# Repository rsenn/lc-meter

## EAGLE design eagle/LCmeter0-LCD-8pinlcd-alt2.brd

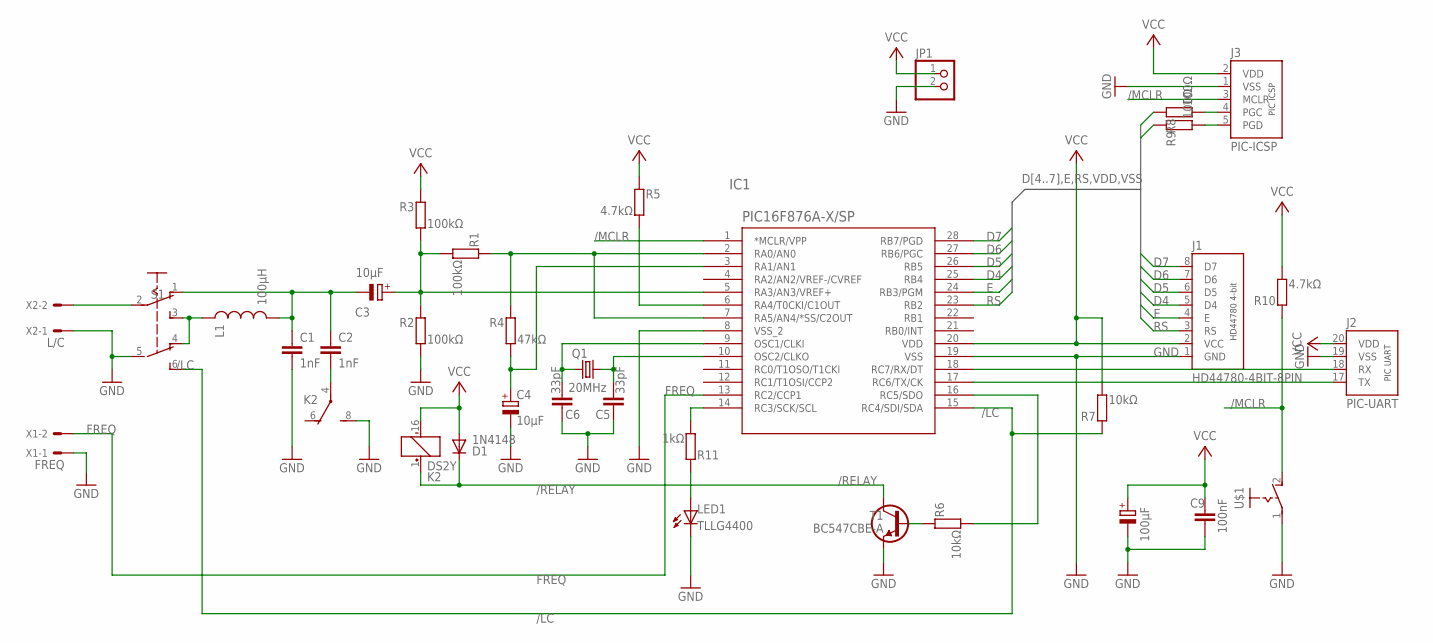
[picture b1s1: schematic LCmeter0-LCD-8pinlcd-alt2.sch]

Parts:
C1, C2: 1nF; C050-020X036
C3, C4: 10μF; E2,5-4
C5, C6: 33pF; C025-020X036
C7: 100μF; E2,5-6
C9: 100nF; C025-024X044
D1: 1N4148; DO34-7
IC1: PIC16F876A-X/SP; DIL28-3
J1: HD44780-4BIT-8PIN; CONN-8P
J2: PIC-UART
J3: PIC-ICSP; CONN-5P
JP1: PINHD-1X2; 1X02
K2: DS2Y
L1: 100μH; L-8R
LED1: TLLG4400; LED3MM
Q1: 20MHz; HC49
R1, R2, R3: 100kΩ; 0202/7
R4: 47kΩ; 0202/7
R5, R10: 4.7kΩ; 0202/7
R6: 10kΩ; 0202/7
R7: 10kΩ; 0202/10
R8, R9: 100Ω; 0202/5
R11: 1kΩ; 0202/5
S1: SL-SW-2P-2T; SLSW-2P2T
T1: BC547CBE-A; TO92-CBE-A
U$1: PB-1P-1T; PB-1P1T
X1: FREQ; 70543-02
X2: L/C; 70543-02

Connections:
/LC: IC1.15 (RC4/SDI/SDA), R7.2, S1.6 (S1)
/MCLR: IC1.1 (*MCLR/VPP), J3.3 (MCLR), R10.2, U$1.2 (S)
/RELAY: D1.C, K2.1 (+), T1.C
A0: IC1.2 (RA0/AN0), IC1.7 (RA5/AN4/*SS/C2OUT), R1.2, R4.2
A1: C4.+, IC1.3 (RA1/AN1), R4.1
A3: C3.+, IC1.5 (RA3/AN3/VREF+), R1.1, R2.2, R3.1
A4: IC1.6 (RA4/T0CKI/C1OUT), R5.1
C2_CON: C2.2, K2.4
D4: IC1.25 (RB4), J1.5 (D4)
D5: IC1.26 (RB5), J1.6 (D5)
D6: IC1.27 (RB6/PGC), J1.7 (D6), R9.2
D7: IC1.28 (RB7/PGD), J1.8 (D7), R8.2
E: IC1.24 (RB3/PGM), J1.4 (E)
FREQ: IC1.13 (RC2/CCP1), X1.2
GND: C1.2, C4.-, C5.1, C6.1, C7.-, C9.2, IC1.8 (VSS_2), IC1.19 (VSS), J1.1 (GND), J2.19 (VSS), J3.1 (VSS), JP1.2, K2.8 (S), LED1.K (C), R2.1, S1.5 (P1), T1.E, U$1.1, X1.1, X2.1
M+: S1.2, X2.2
unnamed: J3.4 (PGC), R8.1
unnamed: C1.1, C2.1, C3.-, L1.P$2 (2), S1.1 (O)
unnamed: J3.5 (PGD), R9.1
unnamed: IC1.14 (RC3/SCK/SCL), R11.1
unnamed: R6.2, T1.B
unnamed: LED1.A, R11.2
unnamed: L1.P$1 (1), S1.3 (S), S1.4 (O1)
unnamed: IC1.17 (RC6/TX/CK), J2.17 (TX)
OSC1: C6.2, IC1.9 (OSC1/CLKI), Q1.1
OSC2: C5.2, IC1.10 (OSC2/CLKO), Q1.2
RC5: IC1.16 (RC5/SDO), R6.1
RS: IC1.23 (RB2), J1.3 (RS)
RX: IC1.18 (RC7/RX/DT), J2.18 (RX)
VCC: C7.+, C9.1, D1.A, IC1.20 (VDD), J1.2 (VCC), J2.20 (VDD), J3.2 (VDD), JP1.1, K2.16 (-), R3.2, R5.2, R7.1, R10.1

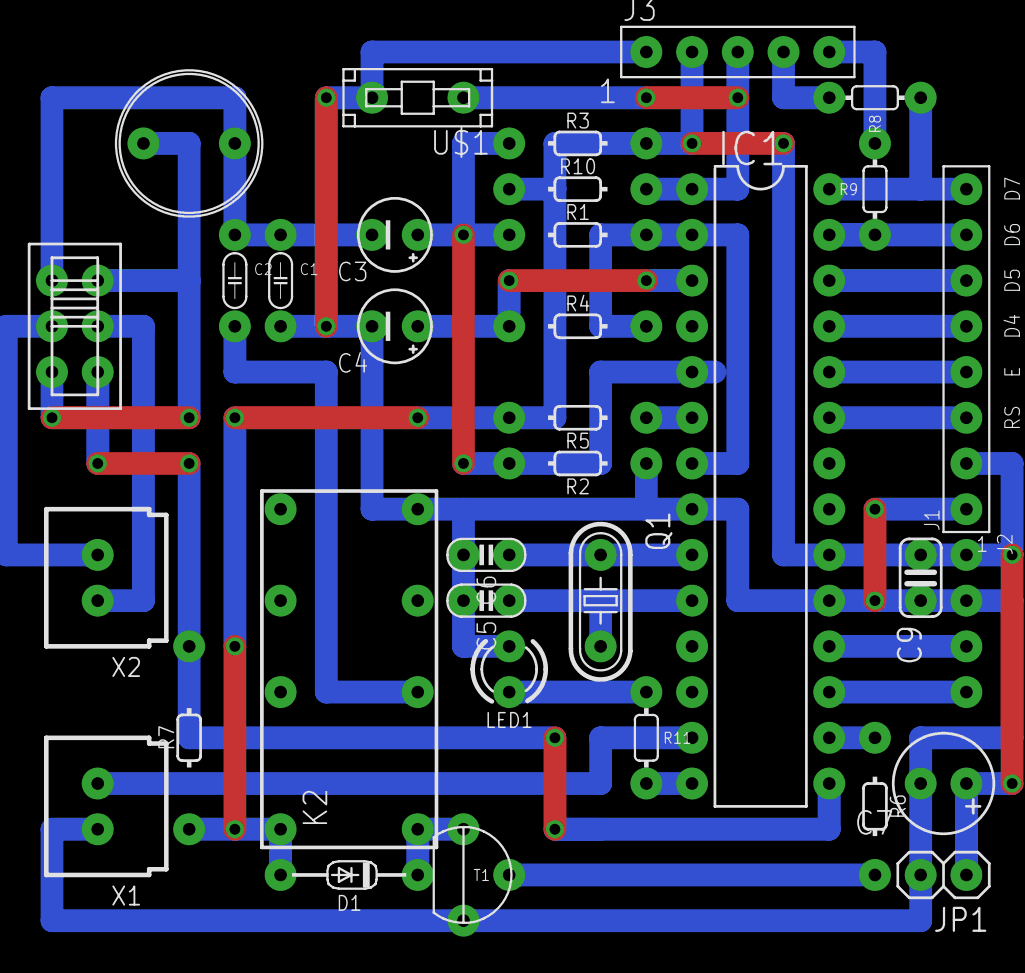
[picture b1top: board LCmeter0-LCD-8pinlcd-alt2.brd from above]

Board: 2 copper layers, 34 parts (0 on the bottom side), 30 nets.

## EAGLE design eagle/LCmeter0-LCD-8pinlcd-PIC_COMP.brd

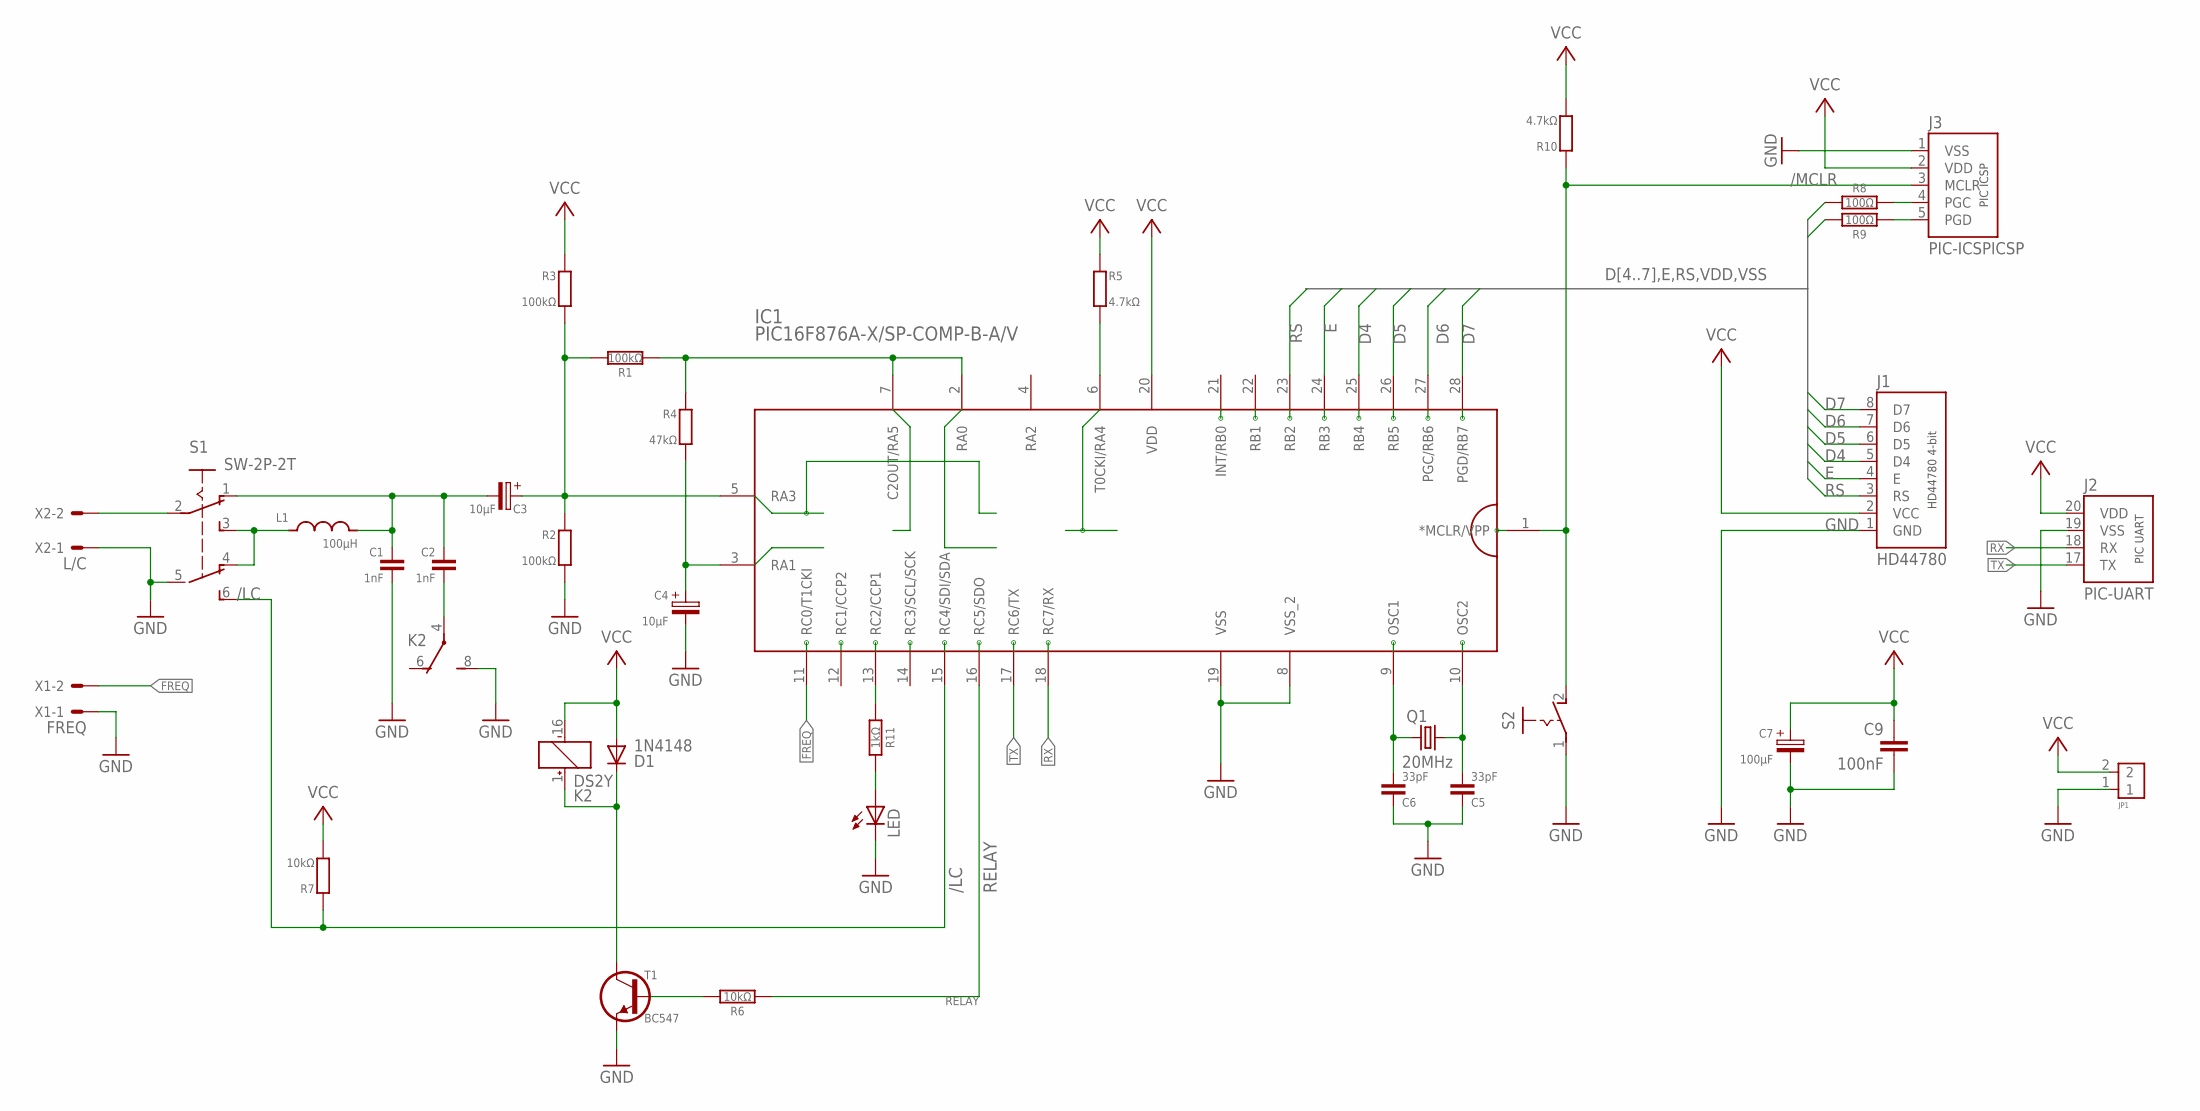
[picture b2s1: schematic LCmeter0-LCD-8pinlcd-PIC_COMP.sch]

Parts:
C1, C2: 1nF; C050-020X036
C3, C4: 10μF; E2,5-4
C5, C6: 33pF; C025-020X036
C7: 100μF; E2,5-5
C9: 100nF; C025-024X044
D1: 1N4148; DO34-7
IC1: PIC16F876A-X/SP-COMP-B-A/V; DIL28-3/V
J1: HD44780; CONN-8P
J2: PIC-UART
J3: PIC-ICSPICSP; PIC-ICSP
JP1: CONN-2P2P/V; CONN-2P-V
K2: DS2Y
L1: 100µH; L-02/5V
LED: TLLG4400; LED3MM
Q1: 20MHz; HC49
R1, R2, R3: 100kΩ; 0202/7
R4: 47kΩ; 0202/7
R5, R10: 4.7kΩ; 0202/7
R6: 10kΩ; 0202/7
R7: 10kΩ; 0202/10
R8, R9: 100Ω; 0202/5
R11: 1kΩ; 0202/5
S1: SW-2P-2T; SLSW-2P2T
S2: PB-1P-1T; PB-1P1T
T1: BC547; TO92-CBE-A
X1: FREQ; 70543-02
X2: L/C; 70543-02

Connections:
/LC: IC1.15 (RC4/SDI/SDA), R7.1, S1.6 (S1)
/MCLR: IC1.1 (*MCLR/VPP), J3.3 (MCLR), R10.1, S2.2 (S)
/RELAY: D1.C, K2.1 (+), T1.C
A0: IC1.2 (RA0), IC1.7 (C2OUT/RA5), R1.1, R4.1
A1: C4.+, IC1.3 (RA1), R4.2
A3: C3.+, IC1.5 (RA3), R1.2, R2.1, R3.2
A4: IC1.6 (T0CKI/RA4), R5.2
C2_CON: C2.2, K2.4
D4: IC1.25 (RB4), J1.5 (D4)
D5: IC1.26 (RB5), J1.6 (D5)
D6: IC1.27 (PGC/RB6), J1.7 (D6), R9.1
D7: IC1.28 (PGD/RB7), J1.8 (D7), R8.1
E: IC1.24 (RB3), J1.4 (E)
FREQ: IC1.11 (RC0/T1CKI), X1.2
GND: C1.2, C4.-, C5.1, C6.1, C7.-, C9.2, IC1.8 (VSS_2), IC1.19 (VSS), J1.1 (GND), J2.19 (VSS), J3.1 (VSS), JP1.1, K2.8 (S), LED.K (C), R2.2, S1.5 (P1), S2.1, T1.E, X1.1, X2.1
M+: S1.2, X2.2
unnamed: J3.4 (PGC), R8.2
unnamed: C1.1, C2.1, C3.-, L1.2, S1.1 (O)
unnamed: J3.5 (PGD), R9.2
unnamed: IC1.13 (RC2/CCP1), R11.2
unnamed: R6.1, T1.B
unnamed: LED.A, R11.1
unnamed: L1.1, S1.3 (S), S1.4 (O1)
OSC1: C6.2, IC1.9 (OSC1), Q1.1
OSC2: C5.2, IC1.10 (OSC2), Q1.2
RELAY: IC1.16 (RC5/SDO), R6.2
RS: IC1.23 (RB2), J1.3 (RS)
RX: IC1.18 (RC7/RX), J2.18 (RX)
TX: IC1.17 (RC6/TX), J2.17 (TX)
VCC: C7.+, C9.1, D1.A, IC1.20 (VDD), J1.2 (VCC), J2.20 (VDD), J3.2 (VDD), JP1.2, K2.16 (-), R3.1, R5.1, R7.2, R10.2

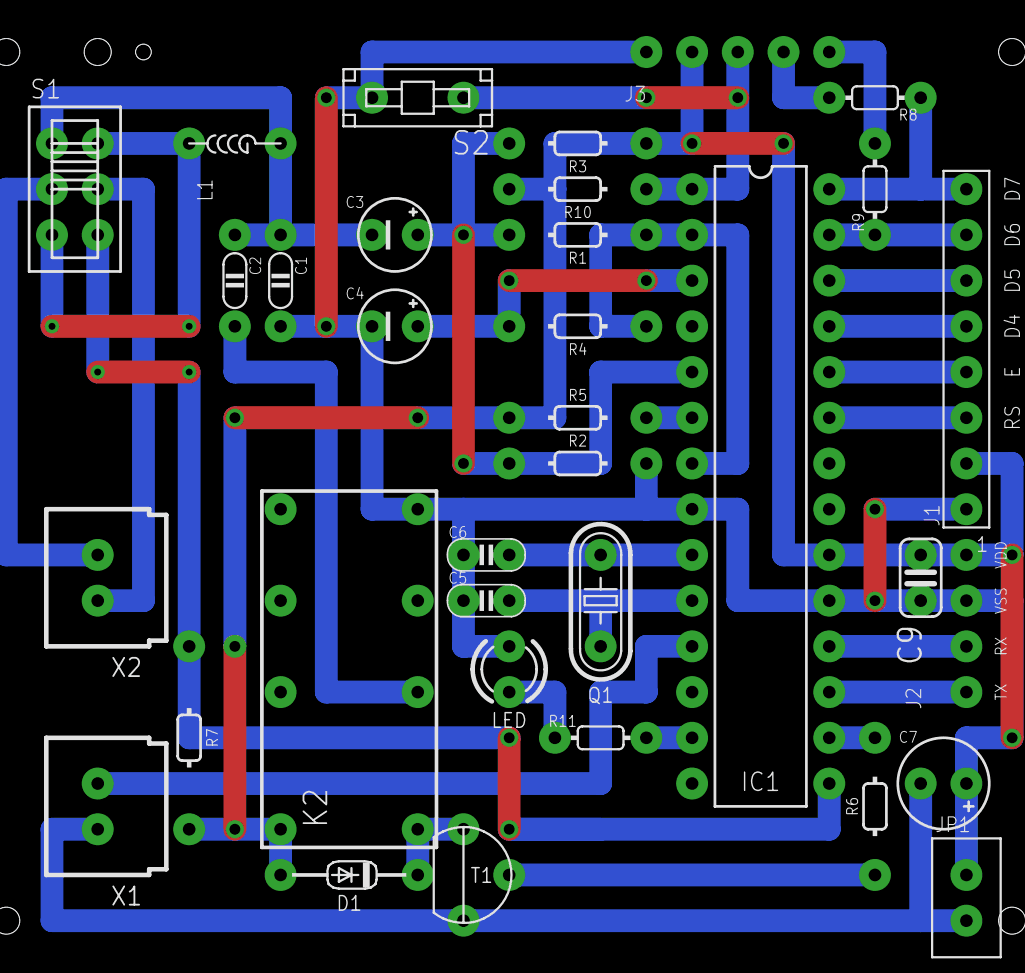
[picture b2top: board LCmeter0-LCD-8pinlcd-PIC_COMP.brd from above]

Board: 2 copper layers, 34 parts (0 on the bottom side), 30 nets.

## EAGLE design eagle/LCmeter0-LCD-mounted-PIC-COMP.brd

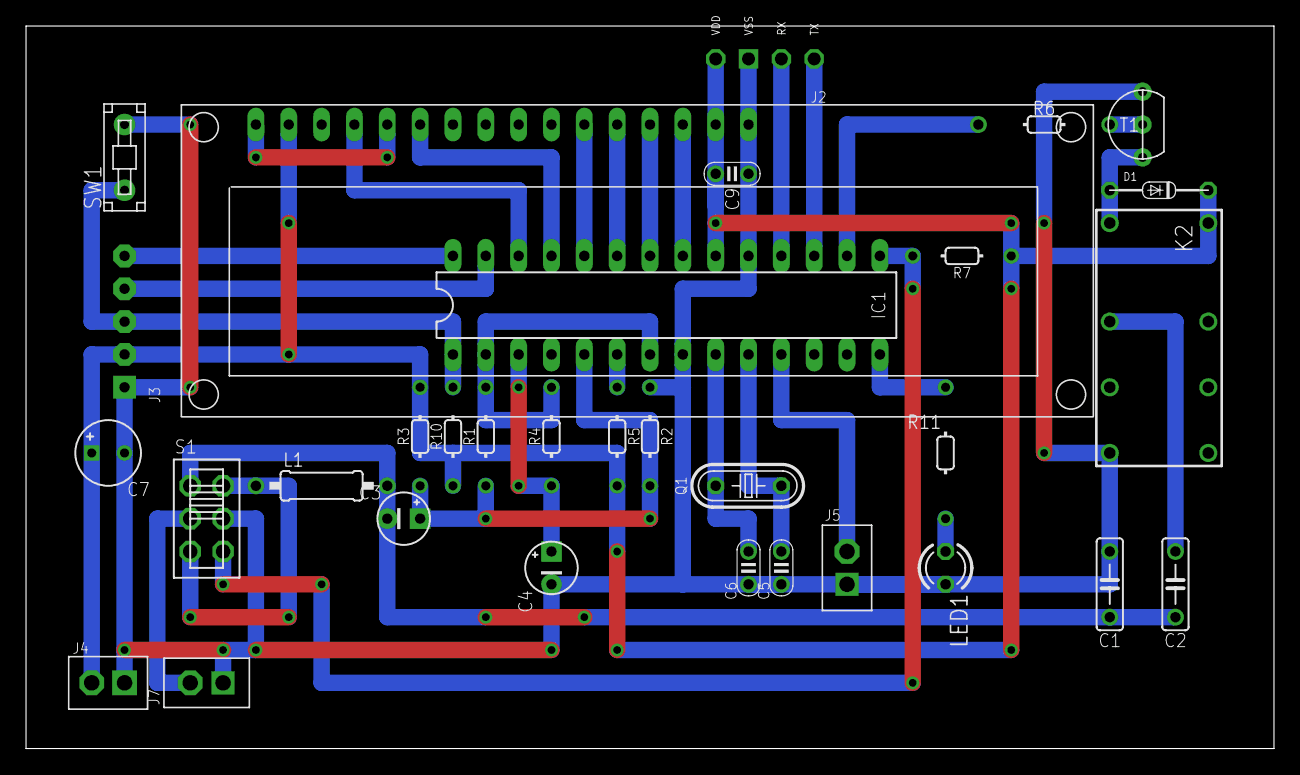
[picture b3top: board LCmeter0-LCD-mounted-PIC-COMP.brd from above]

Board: 2 copper layers, 96.5 x 55.9 mm, 32 parts (0 on the bottom side), 30 nets.

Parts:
C1, C2: 1nF; C050-025X060
C3, C4: 10μF; E2,5-4
C5, C6: 33pF; C025-020X036
C7: 100μF; E2,5-5
C9: 100nF; C025-020X036/V
D1: 1N4148; DO34-7
IC1: PIC16F876A; DIL28-3
J1: HD44780LM016L; LM016L-HD44780
J2: PIC-UART
J3: PIC-ICSP
J4: J4; CONN-2P
J5, J7: CONN-2P2P/V; CONN-2P-V
K2: DS2Y
L1: 82μH; 0207/10
LED1: TLLG4400; LED3MM
Q1: 20MHz; HC49
R1, R2, R3: 100kΩ; 0202/7
R4: 47kΩ; 0202/7
R5, R10: 4.7kΩ; 0202/7
R6: 10kΩ; 0202/10
R7: 10kΩ; 0202/7
R11: 1kΩ; 0202/10-V
S1: SL-SW-2P-2T; SLSW-2P2T
SW1: PB-1P-1T; PB-1P1T
T1: BC547; TO92-CBE

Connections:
/LC: IC1.15, R7.2, S1.6
/MCLR: IC1.1, J3.3, R10.2, SW1.2
/RELAY: D1.A, K2.1, T1.C
A0: IC1.2, IC1.7, R1.2, R4.2
A1: C4.+, IC1.3, R4.1
A3: C3.+, IC1.5, R1.1, R2.2, R3.1
A4: IC1.6, R5.1
C2_CON: C2.2, K2.4
FREQ: IC1.11, J5.2
GND: C1.2, C4.-, C5.1, C6.1, C7.-, C9.1, IC1.8, IC1.19, J1.1, J1.5, J2.19, J3.1, J4.1, J5.1, J7.1, K2.8, LED1.K, R2.1, S1.5, SW1.1, T1.E
IN+: J7.2, S1.2
unnamed: LED1.A, R11.1
unnamed: C1.1, C2.1, C3.-, L1.2, S1.1
unnamed: IC1.14, R11.2
unnamed: R6.2, T1.B
unnamed: L1.1, S1.3, S1.4
unnamed: IC1.16, R6.1
unnamed: IC1.18, J2.18
unnamed: IC1.17, J2.17
OSC1: C6.2, IC1.9, Q1.2
OSC2: C5.2, IC1.10, Q1.1
RB0: IC1.21, J1.14
RB1: IC1.22, J1.13
RB2: IC1.23, J1.12
RB3: IC1.24, J1.11
RB4: IC1.25, J1.6
RB5: IC1.26, J1.4
RB6: IC1.27, J3.4
RB7: IC1.28, J3.5
VCC: C7.+, C9.2, D1.C, IC1.20, J1.2, J2.20, J3.2, J4.2, K2.16, R3.2, R5.2, R7.1, R10.1

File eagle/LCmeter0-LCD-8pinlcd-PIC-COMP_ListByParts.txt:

Part Value                   Attributes Package       Description                                                    Part Num,,
C1   1nF                                C050-025X060  CAPACITOR, European symbol                                     *       ,
C2   1nF                                C050-025X060  CAPACITOR, European symbol                                     *       ,
C3   10µF                               E2,5-4        POLARIZED CAPACITOR, European symbol                           *       
C4   10µF                               E2,5-4        POLARIZED CAPACITOR, European symbol                           *       
C5   33pF                               C025-020X036  CAPACITOR, European symbol                                     *       ,
C6   33pF                               C025-020X036  CAPACITOR, European symbol                                     *       ,
C7   100µF                              E2,5-5        POLARIZED CAPACITOR, European symbol                           *       
C8   22pF                               C050-020X036  CAPACITOR, European symbol                                     *       ,
C9   100nF                              C025-024X044  CAPACITOR, European symbol                                     *       ,
D1   1N4148                             DO34-7                                                                       *       ,,
D2   1N4148                             DO34-12V                                                                     *       ,,
IC1  PIC16F876A                         DIL28-3                                                                      *       ,,
J1   HD44780-4BITLCD44780-8P            CONN-LCD44780                                                                *       ,,
J2   PIC-UART                           PIC-UART                                                                     *       ,,
J3   PIC-ICSP                           PIC-ICSP                                                                     *       ,,
J4   J4                                 CONN-2P                                                                      *       ,,
J5   CONN-2P2P/V                        CONN-2P-V                                                                    *       ,,
J7   CONN-2P2P/V                        CONN-2P-V                                                                    *       ,,
K2   DS2Y                               DS2Y          MINIATURE RELAY NAiS                                           *       ,,
L1   68µH                               L-09R                                                                        *       ,,
LED1 TLLG4400                           LED3MM        Low Current (2mA) LED 3 mm Tinted Diffused Package color GREEN *       ,,
Q1   20MHz                              HC49                                                                         *       ,,
R1   100kO                              0202/7        RESISTOR, European symbol                                      *       ,
R2   100kO                              0202/7        RESISTOR, European symbol                                      *       ,
R3   100kO                              0202/7        RESISTOR, European symbol                                      *       ,
R4   47kO                               0202/7        RESISTOR, European symbol                                      *       ,
R5   4.7kO                              0202/7        RESISTOR, European symbol                                      *       ,
R6   10k                                0202/7-V      RESISTOR, European symbol                                      *       ,
R7   10kO                               0202/10       RESISTOR, European symbol                                      *       ,
R8   100                                0202/7        RESISTOR, European symbol                                      *       ,
R9   100                                0202/5-V      RESISTOR, European symbol                                      *       ,
R10  4.7kO                              0202/7        RESISTOR, European symbol                                      *       ,
R11  1k                                 0202/5-V      RESISTOR, European symbol                                      *       ,
S1   SL-SW-2P-2T-H                      SLSW-2P2T-H                                                                  *       ,,
SW1  PB-1P-1T                           PB-1P1T                                                                      *       ,,
T1   BC547                              TO92-CBE-A                                                                   *       ,,

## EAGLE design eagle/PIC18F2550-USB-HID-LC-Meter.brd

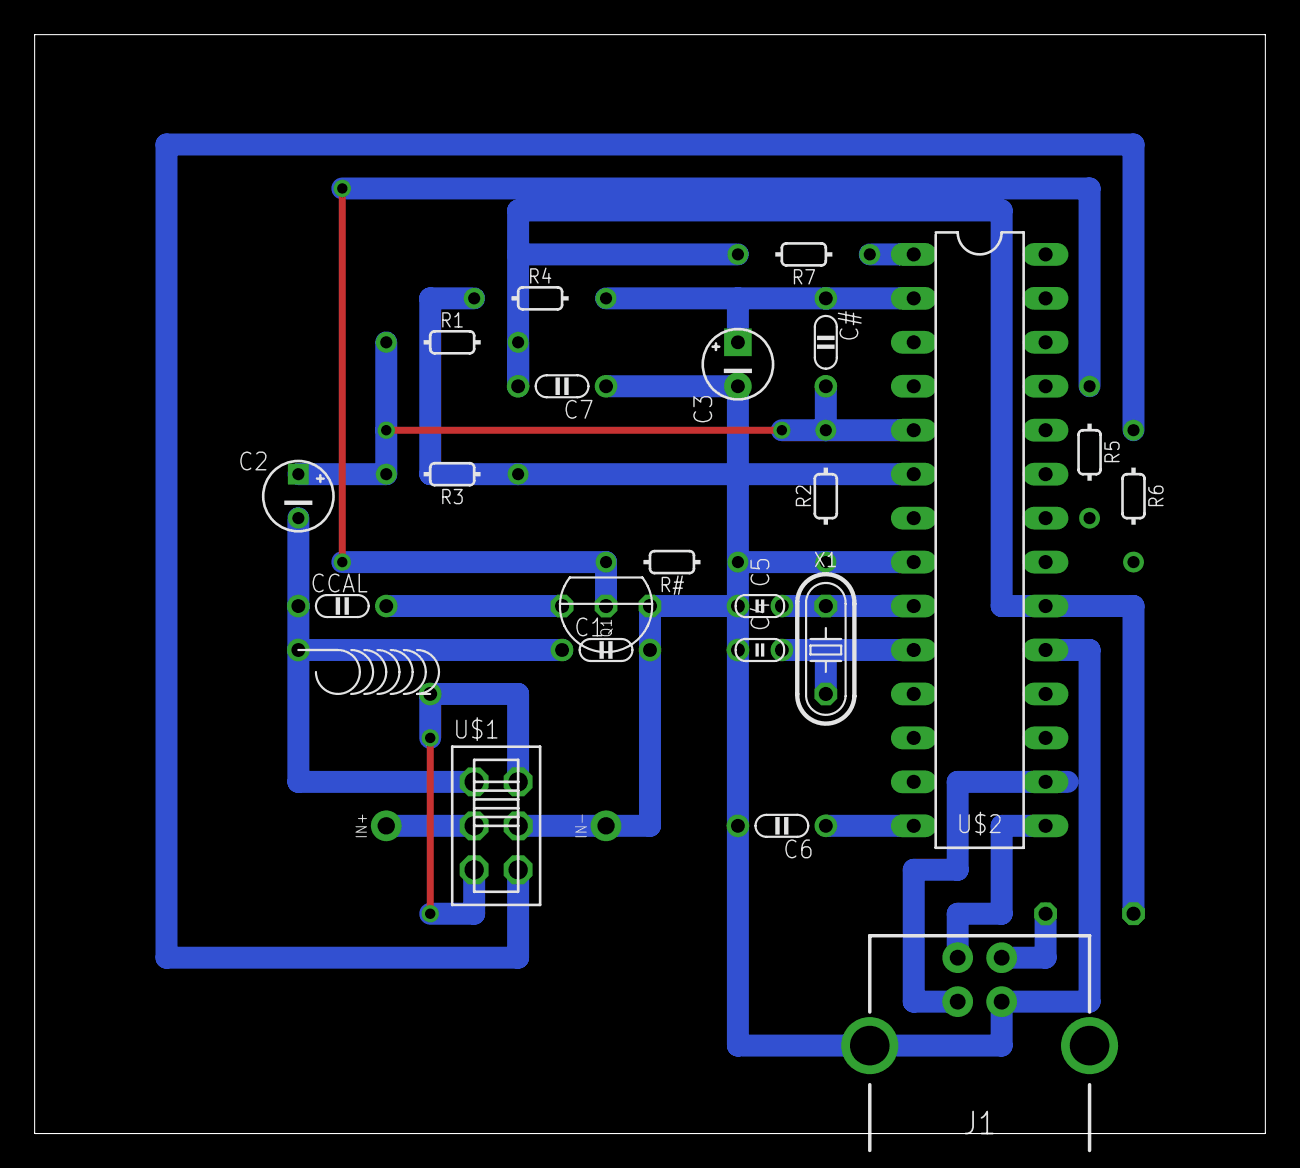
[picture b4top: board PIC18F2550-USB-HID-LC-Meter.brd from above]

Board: 2 copper layers, 71.1 x 63.5 mm, 26 parts (1 on the bottom side), 20 nets.

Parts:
C1: 1n; C050-020X036
C2: 10u; E2.5-4/V
C3: 10u; E2,5-4
C4, C5: 22p; C025-015X024/V
C6: 470n; C050-020X036
C7: C050-020X036
C#: C050-020X036
CCAL: 1n; C050-020X036
D1: 1N414834-5; DO34-5
IN+: SPAD
IN-: SPAD
J1: USB-PRINT; USB-B-PRINT
L1: 100μH; L-04/10-M
Q1: 2N7000; TO92
R1, R2, R3: 100kΩ; 0202/7
R4: 47kΩ; 0202/7
R5, R6: 100Ω; 0202/7
R7: 4.7kΩ; 0202/7
R#: 0202/7
U$1: SW-2P-2T; SLSW-2P2T
U$2: PIC18F2550-I/SP-2-V; DIL28-3/V
X1: 20MHz; HC49

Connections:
GND: C1.2, C3.-, C4.2, C5.2, C6.2, C7.1, IN-.1, J1.GND, Q1.1, R2.1, R#.1, U$1.5, U$2.8, U$2.19
unnamed: Q1.2, R5.1, R#.2
unnamed: R7.1, U$2.1
unnamed: J1.D-, U$2.15
unnamed: J1.D+, U$2.16
unnamed: C2.+, C#.2, R1.1, R2.2, R3.2, U$2.5
unnamed: C3.+, C#.1, R4.2, U$2.2
unnamed: R3.1, R4.1, U$2.6
unnamed: C1.1, C2.-, CCAL.1, L1.2, U$1.1
unnamed: R5.2, U$2.22
unnamed: CCAL.2, Q1.3
unnamed: C4.1, U$2.10, X1.1
unnamed: C5.1, U$2.9, X1.2
unnamed: C6.1, U$2.14
unnamed: L1.1, U$1.3, U$1.4
unnamed: IN+.1, U$1.2
unnamed: R6.1, U$1.6
unnamed: R6.2, U$2.21
VCC: C7.2, D1.C, R1.2, R7.2, U$2.20
VDD: D1.A, J1.VBUS

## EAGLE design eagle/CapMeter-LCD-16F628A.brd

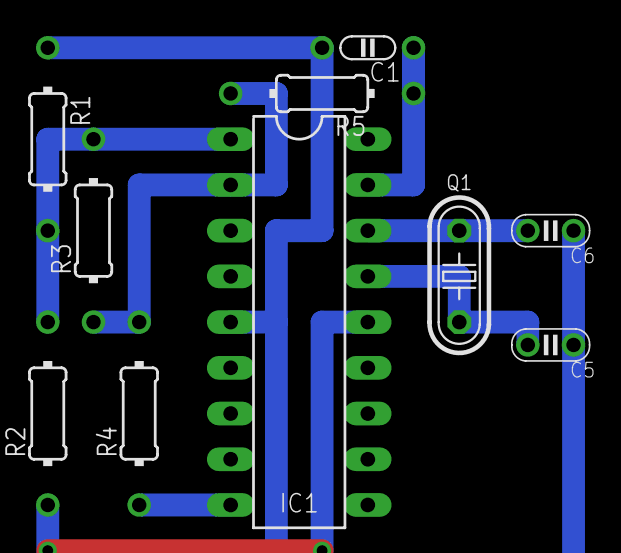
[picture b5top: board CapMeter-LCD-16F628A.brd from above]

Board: 2 copper layers, 10 parts (0 on the bottom side), 8 nets.

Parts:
C1: 270pF; C050-020X036
C5, C6: 33pF; C025-020X036
IC1: PIC16F628A-COMP; DIL18-3/V
Q1: 20MHz; HC49
R1, R2, R3, R4: 1.5kΩ; 0204/10
R5: 10kΩ; 0204/10

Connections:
GND: C1.2, C5.1, C6.1, IC1.5, R1.1
unnamed: IC1.2, R3.1, R4.2, R5.2
unnamed: IC1.9, R4.1
unnamed: IC1.1, R1.2, R2.2, R3.2
unnamed: C1.1, IC1.17, R5.1
OSC1: C6.2, IC1.16, Q1.2
OSC2: C5.2, IC1.15, Q1.1
VCC: IC1.14, R2.1

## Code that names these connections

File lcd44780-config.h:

#ifdef __16f628a
# define RS_PIN  RB5
# define RS_TRIS TRISB5
# undef RW_PIN
# undef RW_TRIS
# define EN_PIN  RB4
# define EN_TRIS TRISB4

#define DATA0_PIN  RA2
#define DATA0_TRIS TRISA2
#define DATA1_PIN  RA3
#define DATA1_TRIS TRISA3
#define DATA2_PIN  RB3
#define DATA2_TRIS TRISB3
#define DATA3_PIN  RB6
#define DATA3_TRIS TRISB6
#else
# define RS_PIN  RB2
# define RS_TRIS TRISB2
# undef RW_PIN
# undef RW_TRIS
# define EN_PIN  RB3    // activated by a HIGH pulse.
# define EN_TRIS TRISB3    // activated by a HIGH pulse.

#define DATA0_PIN  RB4
#define DATA0_TRIS TRISB4
#define DATA1_PIN  RB5
#define DATA1_TRIS TRISB5
#define DATA2_PIN  RB6
#define DATA2_TRIS TRISB6
#define DATA3_PIN  RB7
#define DATA3_TRIS TRISB7
#endif

#ifndef DATABUS_MUX
#define DATABUS_MUX 0
#endif

#if DATABUS_MUX
#define DATABUS_INIT INPUT
#define DATABUS_MUXDELAY 10
#else
#define DATABUS_INIT OUTPUT
#endif

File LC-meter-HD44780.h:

#ifndef MAIN_H
#define MAIN_H

#include "device.h"
#include "oscillator.h"

#ifdef HI_TECH_C
# include <htc.h>  // Required to interface with delay routines
# include <pic.h>
#ifndef nRBPU
volatile unsigned char           OPTION_REG          @ 0x081;

volatile bit nRBPU               @((unsigned)&OPTION_REG * 8) + 7;
//#define nRBPU OPTION_REGbits.nRBPU
#endif
# define NOT_RBPU nRBPU
#endif

#if !defined(HI_TECH_C) && !defined(_BOOSTC) && !defined(__MIKROC_PRO_FOR_PIC__)
# include <pic16f876a.h>
#endif

#ifdef SDCC
#define NOP() __asm("NOP")
#endif

#ifndef SDCC
#define float double
#endif

#include "types.h"
#include "const.h"

#include "lcd44780.h"
///#include "lcd3310.h"

#define M_4_PI_PI 39.47841760435743447527l
#define L_H 0.000330l
#define L_H_1 (1.0/L_H)
#define C_F  0.000000001l
#define C_MF 0.000001l
#define C_UF 0.001l
#define C_NF 1.0l
#define C_PF 1000.0l


#define C_CAL          1000    //pF
#define GATE_PERIOD   100      //ms
#define PI            3.14159
#define LC_SELECT     RC4      //L or C select (from DPDT switch)
#define LC_TRIS()     TRISC4 = INPUT  //as input
#define ADD_CCAL()    RC5 = HIGH    //relay on
#define REMOVE_CCAL() RC5 = LOW    //relay off
#define RELAY_TRIS()  TRISC5 = OUTPUT  //as output to drive the relay coil

//#ifdef HI_TECH_C
# define WITH_LCD 1
//#endif

#define LED_PIN RA2 = RC3
#define LED_TRIS TRISA2 = TRISC3

float measure_freq(void);
float measure_freq_tmr1(void) ;
void calibrate(void);
float calc_capacitance(float);
float calc_inductance(float);
void measure_capacitance(void);
void measure_inductance(void);
void delay10ms(uint16 period_10ms);


#endif // defined(MAIN_H)
